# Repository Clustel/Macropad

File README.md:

# Squish Pad
A fully 3D-printable, true gasket-mounted 4x4 macropad engineered for a premium, ultra-smooth typing experience.

# Features
	16-Key Matrix + Rotary Encoder
	Engineered Leaf-Spring Plate providing a bouncy, trampoline-like typing fee
	Utilizes 3D-printed "slip-on" gasket socks to sandwich the plate tabs, completely isolating the plate and PCB from the outer case.
	Acoustic PCB Cushion

# Rendering

# Schematic

# PCB

# BOM
	1x unsoldered Seeed XIAO RP2040
	16x through-hole 1N4148 Diodes
	15x MX-Style switches
	1x EC11 Rotary encoders
	15x white blank DSA keycaps
	16x SK6812 MINI-E LEDs
	4x M3x16mm screws
	4x M3x5mx4mm heatset inserts
	1x Printed PCB
	1x Case (All parts, guide below)

# Printing Guide

> **If you dont have TPU:** Print the gaskets with PLA/PETG and don't print the cushion. The macropad will still be slightly flexible

| Part | Material | Key Settings |
| :--- | :--- | :--- |
| **Top & Bottom Case** | PLA-CF / PLA | Wall Loops: **5** \| Infill: **25% Gyroid** \| Layer: **0.16mm** |
| **Leaf-Spring Plate** | PETG | Wall Loops: **4** \| Layer: **0.15mm** \| Top/Bottom Layers: **5** |
| **Gaskets (x4)** | 95A TPU | Walls: **2** \| Top/Bottom: **0** \| Infill: **12% Gyroid** \| Speed: **3.5mm³/s** |
| **Cushion** | 95A TPU | Walls: **1** \| Top/Bottom: **0** \| Infill: **6% Gyroid** \| Speed: **3.5mm³/s** |

> **Note:** For the TPU parts, setting Top and Bottom layers to **0** is critical, this exposes the Gyroid infill to create the "squish" effect.

# Assembly guide
_Ensure all 3D-printed parts are cleaned of support material before starting._

> Bottom Case
> 
> 

> Add Cushion (if using TPU)
> 
> 

> Assemble PCB (might be easier to add keycaps in the next step)
> 
> 

> Add Plate
> 
> 

> Put assembly on top of cushion
>
> 

> Put Gaskets on all four sides of plate
> 
> 

> Add top (put heat inserts in the 4 holes)
> 
> 

> Use the screws to attach it together
> 
> 

> Done!
> 
>

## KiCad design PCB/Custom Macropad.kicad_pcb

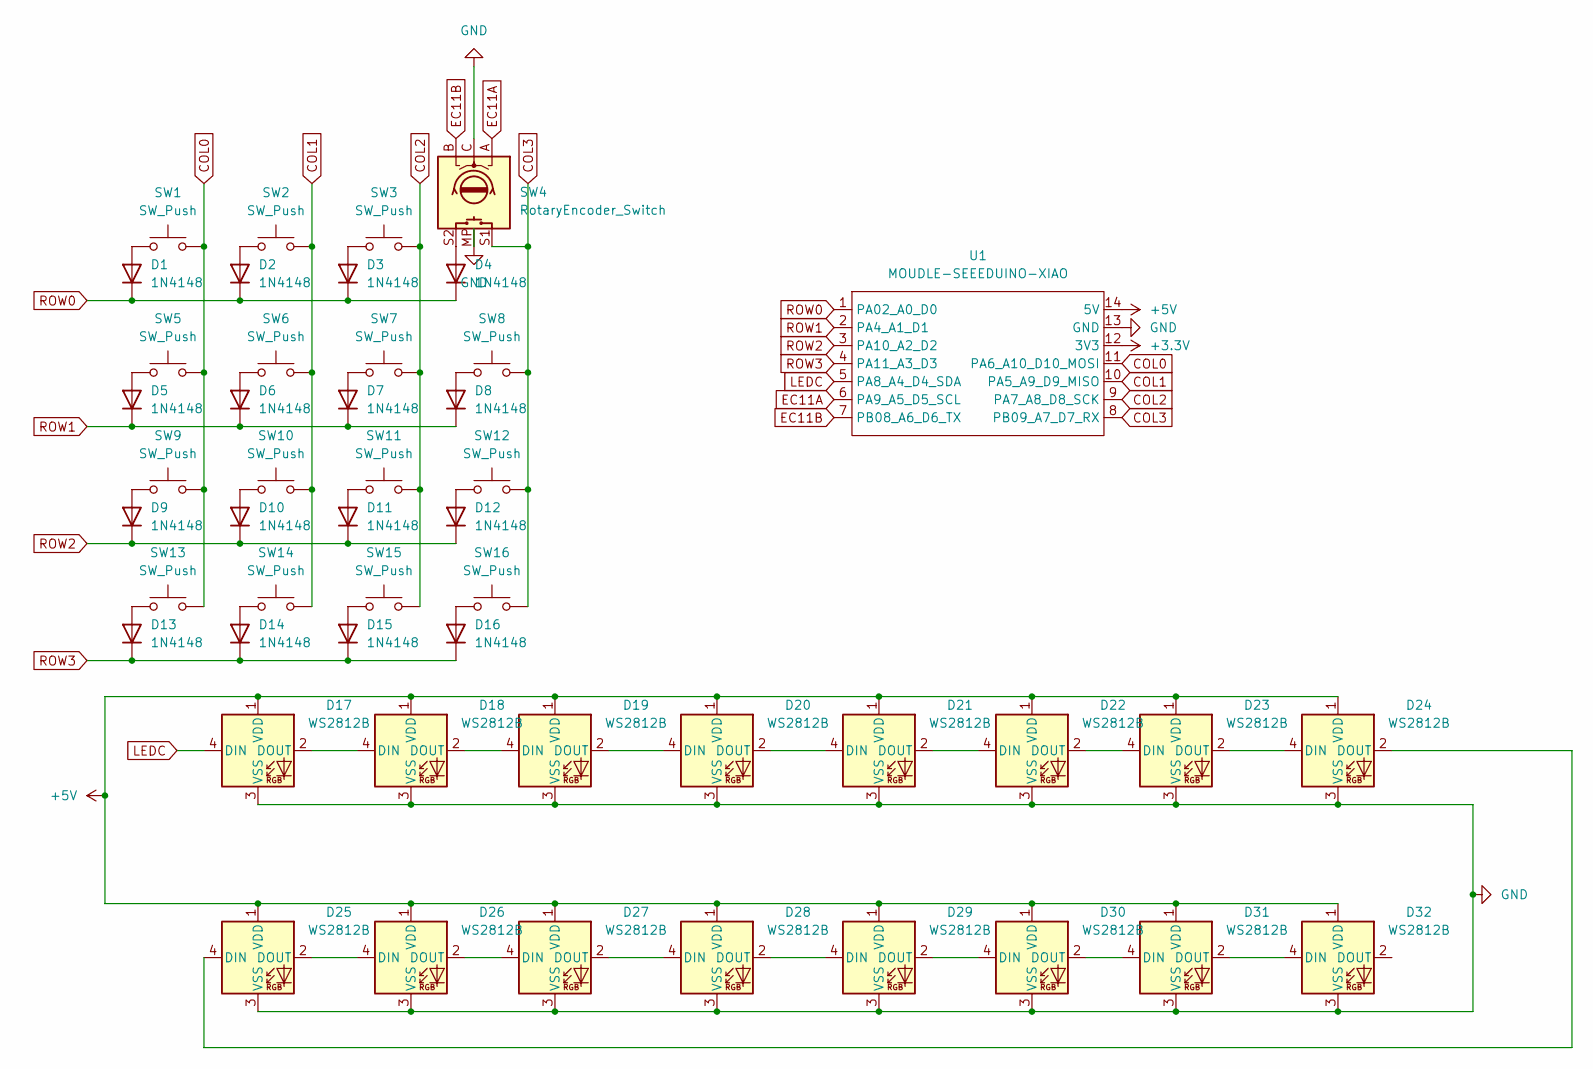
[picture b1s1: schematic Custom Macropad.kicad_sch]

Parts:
D1, D2, D3, D4, D5, D6, D7, D8, D9, D10, D11, D12, D13, D14, D15, D16: 1N4148; D_DO-35_SOD27_P7.62mm_Horizontal
D17, D18, D19, D20, D21, D22, D23, D24, D25, D26, D27, D28, D29, D30, D31, D32: WS2812B; SK6812MINI-E_fixed
SW1, SW2, SW3, SW5, SW6, SW7, SW8, SW9, SW10, SW11, SW12, SW13, SW14, SW15, SW16: SW_Push; SW_Cherry_MX_1.00u_PCB
SW4: RotaryEncoder_Switch; RotaryEncoder_Alps_EC11E-Switch_Vertical_H20mm
U1: MOUDLE-SEEEDUINO-XIAO; XIAO-Generic-Hybrid-14P-2.54-21X17.8MM

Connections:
+3.3V: U1.12 (3V3)
+5V: D17.1 (VDD), D18.1 (VDD), D19.1 (VDD), D20.1 (VDD), D21.1 (VDD), D22.1 (VDD), D23.1 (VDD), D24.1 (VDD), D25.1 (VDD), D26.1 (VDD), D27.1 (VDD), D28.1 (VDD), D29.1 (VDD), D30.1 (VDD), D31.1 (VDD), D32.1 (VDD), U1.14 (5V)
COL0: SW1.2, SW5.2, SW9.2, SW13.2, U1.11 (PA6_A10_D10_MOSI)
COL1: SW2.2, SW6.2, SW10.2, SW14.2, U1.10 (PA5_A9_D9_MISO)
COL2: SW3.2, SW7.2, SW11.2, SW15.2, U1.9 (PA7_A8_D8_SCK)
COL3: SW4.S1, SW8.2, SW12.2, SW16.2, U1.8 (PB09_A7_D7_RX)
EC11A: SW4.A, U1.6 (PA9_A5_D5_SCL)
EC11B: SW4.B, U1.7 (PB08_A6_D6_TX)
GND: D17.3 (VSS), D18.3 (VSS), D19.3 (VSS), D20.3 (VSS), D21.3 (VSS), D22.3 (VSS), D23.3 (VSS), D24.3 (VSS), D25.3 (VSS), D26.3 (VSS), D27.3 (VSS), D28.3 (VSS), D29.3 (VSS), D30.3 (VSS), D31.3 (VSS), D32.3 (VSS), SW4.C, SW4.MP (Shield), U1.13 (GND)
LEDC: D17.4 (DIN), U1.5 (PA8_A4_D4_SDA)
unnamed: D1.2 (A), SW1.1
unnamed: D2.2 (A), SW2.1
unnamed: D3.2 (A), SW3.1
unnamed: D4.2 (A), SW4.S2
unnamed: D5.2 (A), SW5.1
unnamed: D6.2 (A), SW6.1
unnamed: D7.2 (A), SW7.1
unnamed: D8.2 (A), SW8.1
unnamed: D9.2 (A), SW9.1
unnamed: D10.2 (A), SW10.1
unnamed: D11.2 (A), SW11.1
unnamed: D12.2 (A), SW12.1
unnamed: D13.2 (A), SW13.1
unnamed: D14.2 (A), SW14.1
unnamed: D15.2 (A), SW15.1
unnamed: D16.2 (A), SW16.1
unnamed: D17.2 (DOUT), D18.4 (DIN)
unnamed: D18.2 (DOUT), D19.4 (DIN)
unnamed: D19.2 (DOUT), D20.4 (DIN)
unnamed: D20.2 (DOUT), D21.4 (DIN)
unnamed: D21.2 (DOUT), D22.4 (DIN)
unnamed: D22.2 (DOUT), D23.4 (DIN)
unnamed: D23.2 (DOUT), D24.4 (DIN)
unnamed: D24.2 (DOUT), D25.4 (DIN)
unnamed: D25.2 (DOUT), D26.4 (DIN)
unnamed: D26.2 (DOUT), D27.4 (DIN)
unnamed: D27.2 (DOUT), D28.4 (DIN)
unnamed: D28.2 (DOUT), D29.4 (DIN)
unnamed: D29.2 (DOUT), D30.4 (DIN)
unnamed: D30.2 (DOUT), D31.4 (DIN)
unnamed: D31.2 (DOUT), D32.4 (DIN)
ROW0: D1.1 (K), D2.1 (K), D3.1 (K), D4.1 (K), U1.1 (PA02_A0_D0)
ROW1: D5.1 (K), D6.1 (K), D7.1 (K), D8.1 (K), U1.2 (PA4_A1_D1)
ROW2: D9.1 (K), D10.1 (K), D11.1 (K), D12.1 (K), U1.3 (PA10_A2_D2)
ROW3: D13.1 (K), D14.1 (K), D15.1 (K), D16.1 (K), U1.4 (PA11_A3_D3)

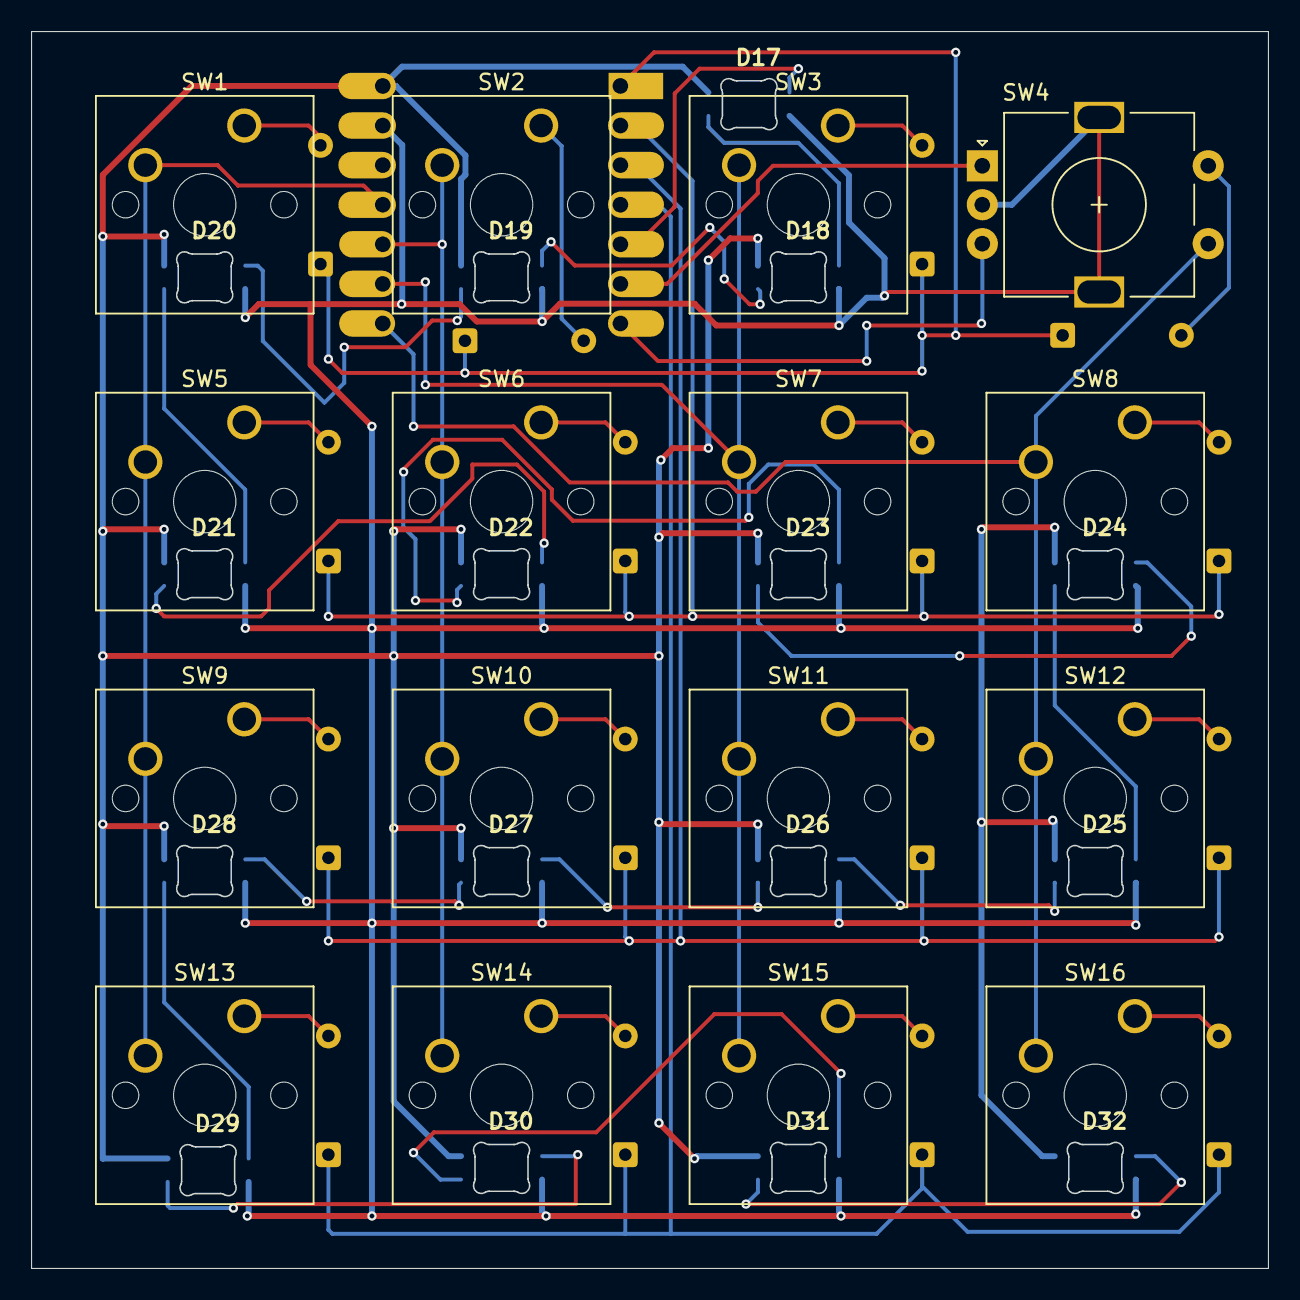
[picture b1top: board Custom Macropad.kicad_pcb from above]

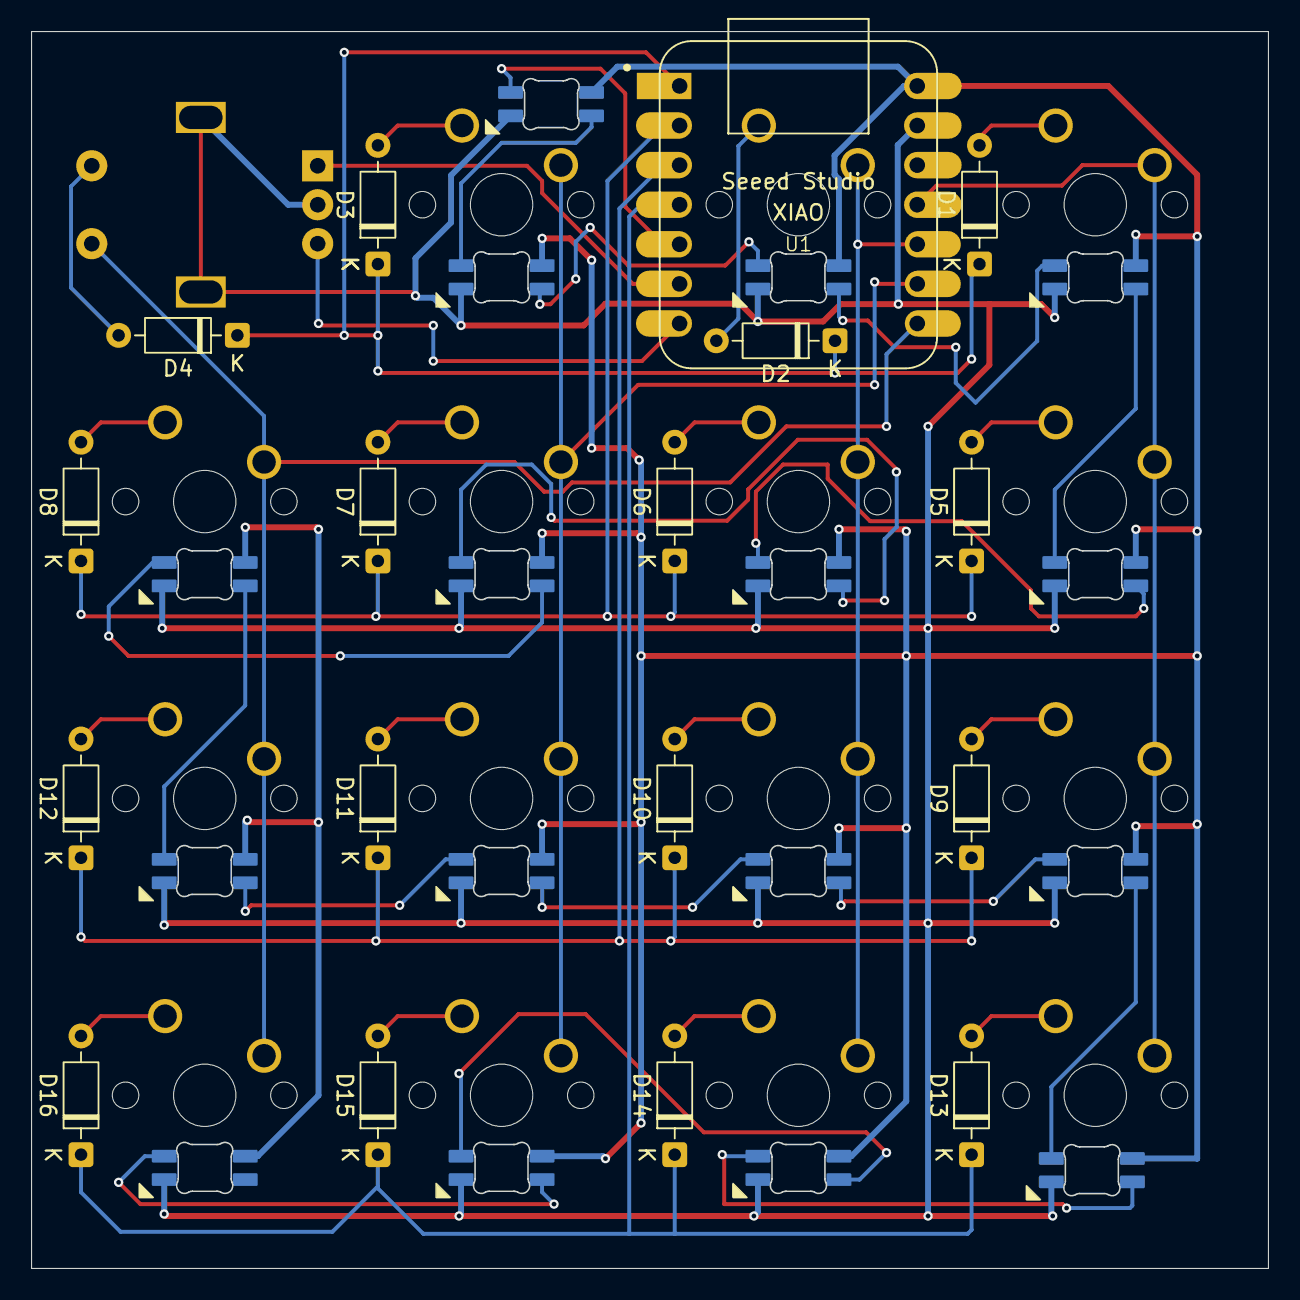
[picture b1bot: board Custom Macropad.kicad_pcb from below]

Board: 2 copper layers, 79.3 x 79.3 mm, 49 parts (17 on the bottom side), 44 nets.

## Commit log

2026-02-12 First Schematic Iteration
2026-02-13 Schematic V1
2026-02-19 Key pcb layout
2026-02-19 full pcb layout done w/o routing
2026-02-19 Finished routing v1
2026-02-27 Final
2026-02-28 Final v2
2026-02-28 needed files
2026-03-02 README v1
    Clarified note about TPU parts and infill settings.
2026-03-02 renamed to PCB
2026-03-02 Add PCB and case to parts list in README
2026-03-02 Added assembly guide
    Updated assembly guide with new image sizes and instructions.
2026-03-03 Refactor main.py by removing comments and cleaning code
